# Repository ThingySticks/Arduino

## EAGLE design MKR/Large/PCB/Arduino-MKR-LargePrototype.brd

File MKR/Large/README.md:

Large Prototyping PCB for Arduino MKR Series
============================================

Suitable for:

* Arduino MKR Zero
* Arduino MKR 1000 WiFi
* Arduino MKR FOX 1200
* Arduino MKR WAN 1300
* Arduino MKR GSM 1000

[Available on Tindie](https://www.tindie.com/products/ThingySticks/large-prototype-pcb-for-the-arduino-mkr-series/)

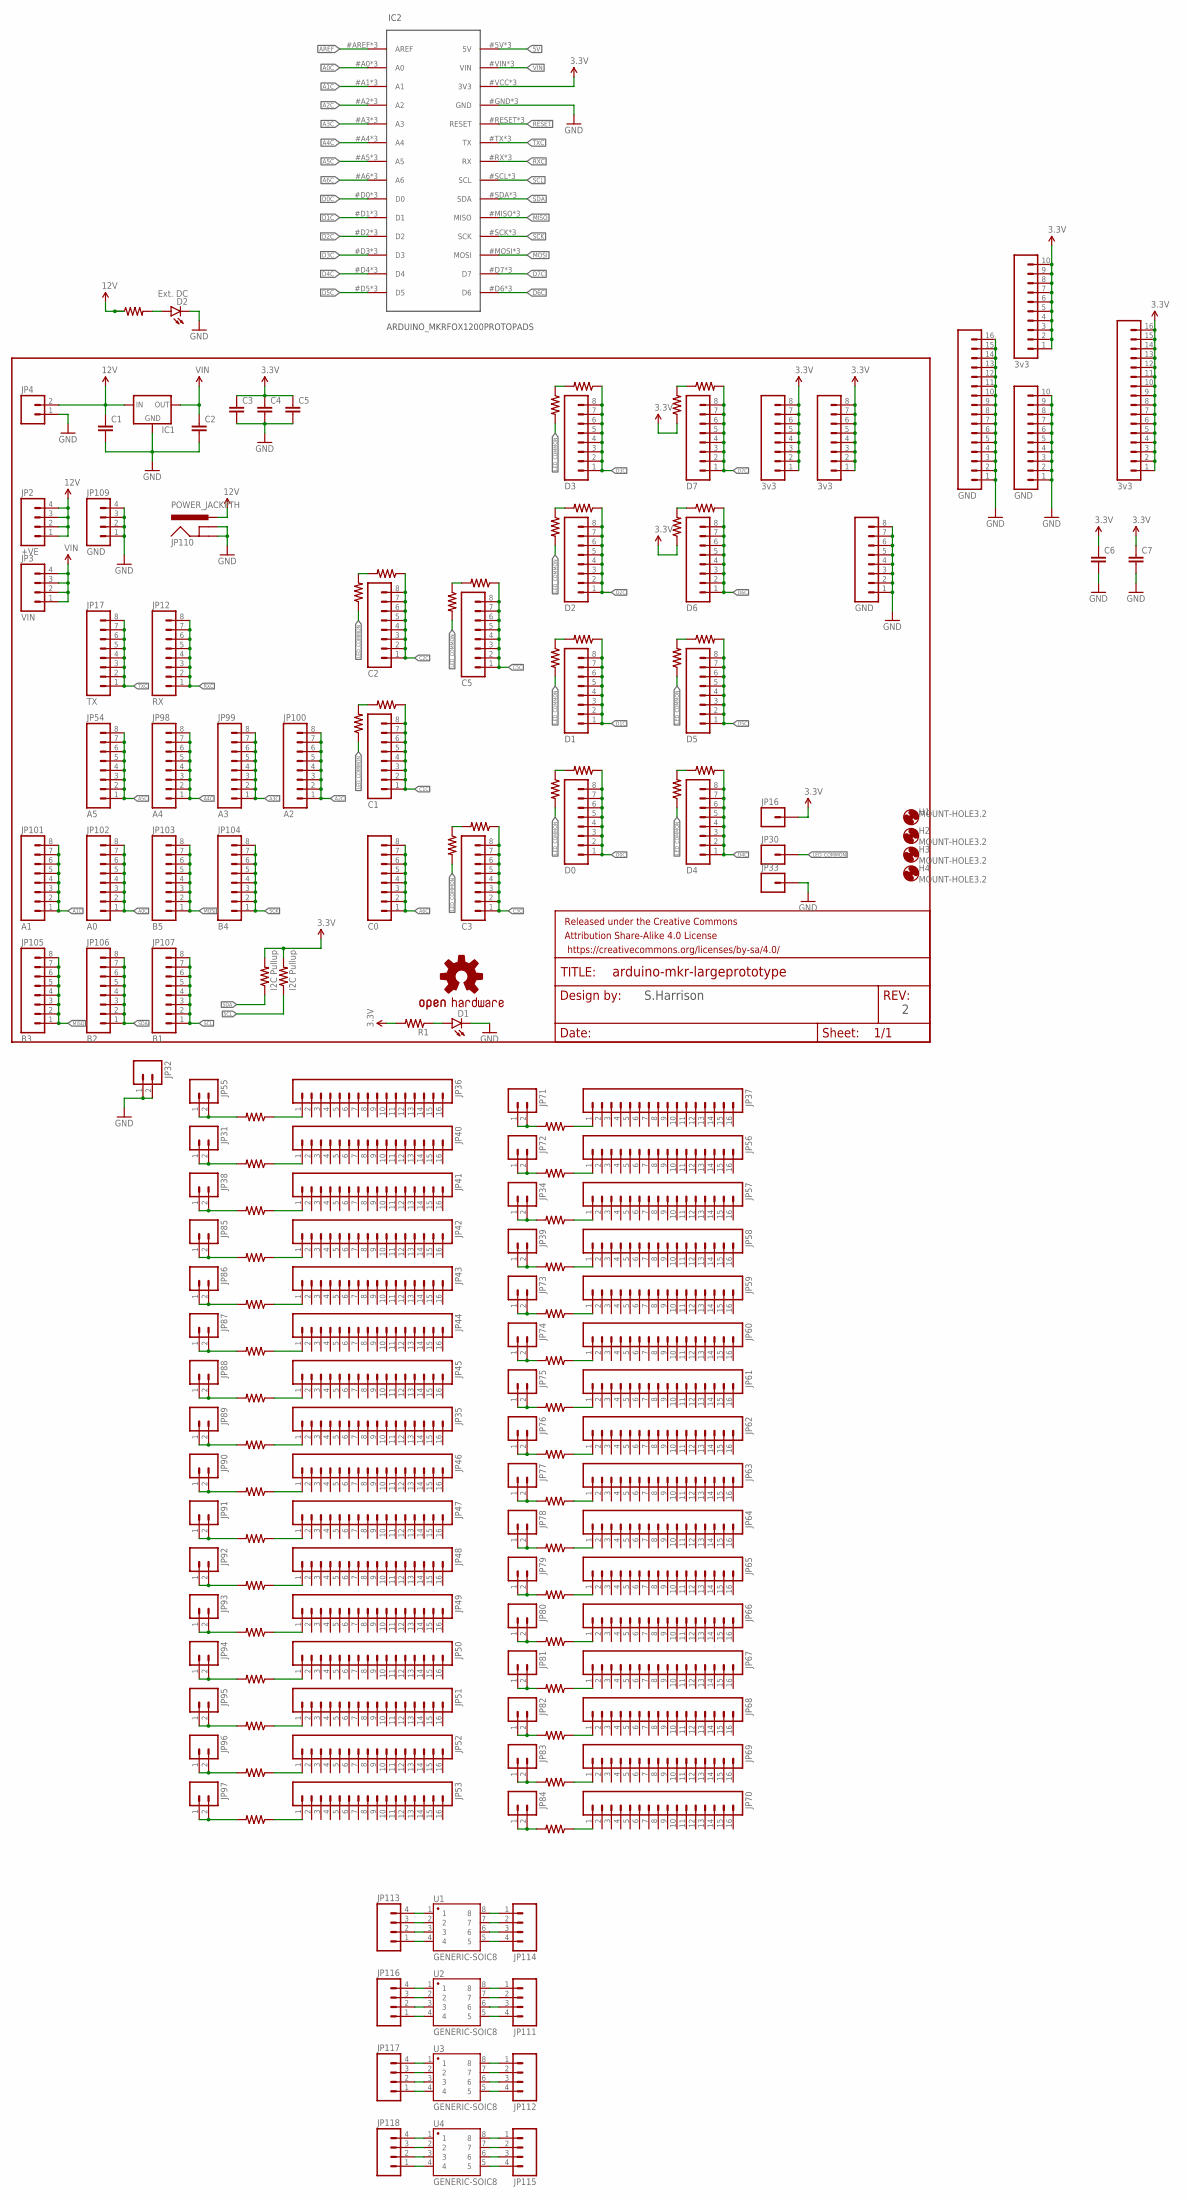
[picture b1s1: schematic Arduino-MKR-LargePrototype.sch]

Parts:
3V1, 3V3: 3v3; 1X08_ROUND
C1, C2, C3, C4, C5, C6, C7: 1UF-25V-10%(0805)"; 0805-CAP
D1: LED1206-BOTTOM; LED-1206-BOTTOM
D2: Ext. DC; LED-1206
FRAME1: FRAME-LETTER; CREATIVE_COMMONS
H1, H2, H3, H4: MOUNT-HOLE3.2; 3,2
IC1: 78XXS
IC2: ARDUINO_MKRFOX1200PROTOPADS; ARDUINO_MKRFOX1200_PROTOPADS
JP1: D7; 1X08_ROUND
JP2: +VE; 1X04
JP3: VIN; 1X04
JP4: M025MM; SCREWTERMINAL-5MM-2
JP5: 3v3; 1X10
JP7: D6; 1X08_ROUND
JP10: D5; 1X08_ROUND
JP11: GND; 1X10
JP12: RX; 1X08_ROUND
JP13: 3v3; 1X16
JP14: GND; 1X16
JP16, JP30, JP33: M01PTH; 1X01
JP17: TX; 1X08_ROUND
JP18: D4; 1X08_ROUND
JP19: D3; 1X08_ROUND
JP20: D2; 1X08_ROUND
JP21: D1; 1X08_ROUND
JP22: D0; 1X08_ROUND
JP23: GND; 1X08_ROUND
JP24: C5; 1X08_ROUND
JP26: C3; 1X08_ROUND
JP27: C2; 1X08_ROUND
JP28: C1; 1X08_ROUND
JP29: C0; 1X08_ROUND
JP31, JP32, JP34, JP38, JP39, JP55, JP71, JP72, JP73, JP74, JP75, JP76, JP77, JP78, JP79, JP80, JP81, JP82, JP83, JP84, JP85, JP86, JP87, JP88, JP89, JP90, JP91, JP92, JP93, JP94, JP95, JP96, JP97: M02PTH; 1X02
JP35, JP36, JP37, JP40, JP41, JP42, JP43, JP44, JP45, JP46, JP47, JP48, JP49, JP50, JP51, JP52, JP53, JP56, JP57, JP58, JP59, JP60, JP61, JP62, JP63, JP64, JP65, JP66, JP67, JP68, JP69, JP70: M161X16_NO_SILK; 1X16_NO_SILK
JP54: A5; 1X08_ROUND
JP98: A4; 1X08_ROUND
JP99: A3; 1X08_ROUND
JP100: A2; 1X08_ROUND
JP101: A1; 1X08_ROUND
JP102: A0; 1X08_ROUND
JP103: B5; 1X08_ROUND
JP104: B4; 1X08_ROUND
JP105: B3; 1X08_ROUND
JP106: B2; 1X08_ROUND
JP107: B1; 1X08_ROUND
JP109: GND; 1X04
JP110: POWER_JACKPTH; POWER_JACK_PTH
JP111, JP112, JP113, JP114, JP115, JP116, JP117, JP118: M04NO_SILK_ALL_ROUND; 1X04_NO_SILK_ALL_ROUND
LOGO3: OSHW-LOGOM; OSHW-LOGO-M
R1, R2, R3, R4, R5, R6, R7, R8, R9, R10, R11, R12, R13, R14, R15, R16, R17, R18, R19, R22, R23, R24, R25, R26, R27, R28, R30, R31, R32, R33, R34, R35, R36, R37, R38, R39, R40, R41, R42, R43, R44, R45, R46, R47, R48, R49, R50, R51, R52, R53, R54, R55, R56, R57, R58, R59, R60, R61: RESISTOR1206; 1206
R64, R65: I2C Pullup; 1206
U1, U2, U3, U4: GENERIC-SOIC8; SO08-UNIVERSAL

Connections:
3.3V: 3V1.1, 3V1.2, 3V1.3, 3V1.4, 3V1.5, 3V1.6, 3V1.7, 3V1.8, 3V3.1, 3V3.2, 3V3.3, 3V3.4, 3V3.5, 3V3.6, 3V3.7, 3V3.8, C3.1, C4.1, C5.1, C6.1, C7.1, IC2.#VCC (3V3), IC2.@VCC (3V3), IC2.VCC (3V3), JP5.1, JP5.2, JP5.3, JP5.4, JP5.5, JP5.6, JP5.7, JP5.8, JP5.9, JP5.10, JP13.1, JP13.2, JP13.3, JP13.4, JP13.5, JP13.6, JP13.7, JP13.8, JP13.9, JP13.10, JP13.11, JP13.12, JP13.13, JP13.14, JP13.15, JP13.16, JP16.1, R1.2, R2.1, R5.1, R64.2, R65.2
5V: IC2.5V, IC2.#5V (5V), IC2.@5V (5V)
12V: C1.1, IC1.IN, JP2.1, JP2.2, JP2.3, JP2.4, JP4.2, JP110.PWR, R28.1
A0C: IC2.#A0 (A0), IC2.@A0 (A0), IC2.A0, JP102.1, JP102.2, JP102.3, JP102.4, JP102.5, JP102.6, JP102.7, JP102.8
A1C: IC2.#A1 (A1), IC2.@A1 (A1), IC2.A1, JP101.1, JP101.2, JP101.3, JP101.4, JP101.5, JP101.6, JP101.7, JP101.8
A2C: IC2.#A2 (A2), IC2.@A2 (A2), IC2.A2, JP100.1, JP100.2, JP100.3, JP100.4, JP100.5, JP100.6, JP100.7, JP100.8
A3C: IC2.#A3 (A3), IC2.@A3 (A3), IC2.A3, JP99.1, JP99.2, JP99.3, JP99.4, JP99.5, JP99.6, JP99.7, JP99.8
A4C: IC2.#A4 (A4), IC2.@A4 (A4), IC2.A4, JP98.1, JP98.2, JP98.3, JP98.4, JP98.5, JP98.6, JP98.7, JP98.8
A5C: IC2.#A5 (A5), IC2.@A5 (A5), IC2.A5, JP54.1, JP54.2, JP54.3, JP54.4, JP54.5, JP54.6, JP54.7, JP54.8
A6C: IC2.#A6 (A6), IC2.@A6 (A6), IC2.A6, JP29.1, JP29.2, JP29.3, JP29.4, JP29.5, JP29.6, JP29.7, JP29.8
AREF: IC2.#AREF (AREF), IC2.@AREF (AREF), IC2.AREF
C1C: JP28.1, JP28.2, JP28.3, JP28.4, JP28.5, JP28.6, JP28.7, JP28.8, R26.1
C2C: JP27.1, JP27.2, JP27.3, JP27.4, JP27.5, JP27.6, JP27.7, JP27.8, R24.1
C3C: JP26.1, JP26.2, JP26.3, JP26.4, JP26.5, JP26.6, JP26.7, JP26.8, R22.1
C5C: JP24.1, JP24.2, JP24.3, JP24.4, JP24.5, JP24.6, JP24.7, JP24.8, R18.1
D0C: IC2.#D0 (D0), IC2.@D0 (D0), IC2.D0, JP22.1, JP22.2, JP22.3, JP22.4, JP22.5, JP22.6, JP22.7, JP22.8, R16.1
D1C: IC2.#D1 (D1), IC2.@D1 (D1), IC2.D1, JP21.1, JP21.2, JP21.3, JP21.4, JP21.5, JP21.6, JP21.7, JP21.8, R14.1
D2C: IC2.#D2 (D2), IC2.@D2 (D2), IC2.D2, JP20.1, JP20.2, JP20.3, JP20.4, JP20.5, JP20.6, JP20.7, JP20.8, R12.1
D3C: IC2.#D3 (D3), IC2.@D3 (D3), IC2.D3, JP19.1, JP19.2, JP19.3, JP19.4, JP19.5, JP19.6, JP19.7, JP19.8, R10.1
D4C: IC2.#D4 (D4), IC2.@D4 (D4), IC2.D4, JP18.1, JP18.2, JP18.3, JP18.4, JP18.5, JP18.6, JP18.7, JP18.8, R8.2
D5C: IC2.#D5 (D5), IC2.@D5 (D5), IC2.D5, JP10.1, JP10.2, JP10.3, JP10.4, JP10.5, JP10.6, JP10.7, JP10.8, R6.2
D6C: IC2.#D6 (D6), IC2.@D6 (D6), IC2.D6, JP7.1, JP7.2, JP7.3, JP7.4, JP7.5, JP7.6, JP7.7, JP7.8, R4.2
D7C: IC2.#D7 (D7), IC2.@D7 (D7), IC2.D7, JP1.1, JP1.2, JP1.3, JP1.4, JP1.5, JP1.6, JP1.7, JP1.8, R3.2
GND: C1.2, C2.2, C3.2, C4.2, C5.2, C6.2, C7.2, D1.C, D2.C, IC1.GND, IC2.#GND (GND), IC2.@GND (GND), IC2.GND, JP4.1, JP11.1, JP11.2, JP11.3, JP11.4, JP11.5, JP11.6, JP11.7, JP11.8, JP11.9, JP11.10, JP14.1, JP14.2, JP14.3, JP14.4, JP14.5, JP14.6, JP14.7, JP14.8, JP14.9, JP14.10, JP14.11, JP14.12, JP14.13, JP14.14, JP14.15, JP14.16, JP23.1, JP23.2, JP23.3, JP23.4, JP23.5, JP23.6, JP23.7, JP23.8, JP32.1, JP32.2, JP33.1, JP109.1, JP109.2, JP109.3, JP109.4, JP110.GND, JP110.GNDBREAK
LED_COMMON: JP30.1, R7.1, R9.1, R11.2, R13.2, R15.2, R17.2, R19.2, R23.2, R25.1, R27.1
MISO: IC2.#MISO (MISO), IC2.@MISO (MISO), IC2.MISO, JP105.1, JP105.2, JP105.3, JP105.4, JP105.5, JP105.6, JP105.7, JP105.8
MOSI: IC2.#MOSI (MOSI), IC2.@MOSI (MOSI), IC2.MOSI, JP103.1, JP103.2, JP103.3, JP103.4, JP103.5, JP103.6, JP103.7, JP103.8
unnamed: D1.A, R1.1
unnamed: JP113.4, U1.1
unnamed: JP113.3, U1.2
unnamed: R4.1, R5.2
unnamed: R2.2, R3.1
unnamed: R10.2, R11.1
unnamed: JP113.2, U1.3
unnamed: JP113.1, U1.4
unnamed: JP114.1, U1.8
unnamed: R8.1, R9.2
unnamed: R6.1, R7.2
unnamed: JP114.2, U1.7
unnamed: R12.2, R13.1
unnamed: R14.2, R15.1
unnamed: R16.2, R17.1
unnamed: JP114.3, U1.6
unnamed: JP114.4, U1.5
unnamed: JP116.4, U2.1
unnamed: R18.2, R19.1
unnamed: JP116.3, U2.2
unnamed: JP116.2, U2.3
unnamed: R22.2, R23.1
unnamed: JP71.1, JP71.2, R46.2
unnamed: JP116.1, U2.4
unnamed: R26.2, R27.2
unnamed: JP117.4, U3.1
unnamed: R24.2, R25.2
unnamed: JP117.3, U3.2
unnamed: JP72.1, JP72.2, R47.2
unnamed: JP34.1, JP34.2, R48.2
unnamed: JP39.1, JP39.2, R49.2
unnamed: JP73.1, JP73.2, R50.2
unnamed: JP74.1, JP74.2, R51.2
unnamed: JP75.1, JP75.2, R52.2
unnamed: JP76.1, JP76.2, R53.2
unnamed: JP77.1, JP77.2, R54.2
unnamed: JP78.1, JP78.2, R55.2
unnamed: JP79.1, JP79.2, R56.2
unnamed: JP80.1, JP80.2, R57.2
unnamed: JP81.1, JP81.2, R58.2
unnamed: JP82.1, JP82.2, R59.2
unnamed: JP83.1, JP83.2, R60.2
unnamed: JP84.1, JP84.2, R61.2
unnamed: JP70.1, R61.1
unnamed: JP69.1, R60.1
unnamed: JP68.1, R59.1
unnamed: JP67.1, R58.1
unnamed: JP66.1, R57.1
unnamed: JP65.1, R56.1
unnamed: JP64.1, R55.1
unnamed: JP63.1, R54.1
unnamed: JP62.1, R53.1
unnamed: JP61.1, R52.1
unnamed: JP60.1, R51.1
unnamed: JP59.1, R50.1
unnamed: JP58.1, R49.1
unnamed: JP57.1, R48.1
unnamed: JP56.1, R47.1
unnamed: JP37.1, R46.1
unnamed: JP97.1, JP97.2, R45.2
unnamed: JP96.1, JP96.2, R44.2
unnamed: JP95.1, JP95.2, R43.2
unnamed: JP94.1, JP94.2, R42.2
unnamed: JP93.1, JP93.2, R41.2
unnamed: JP92.1, JP92.2, R40.2
unnamed: JP91.1, JP91.2, R39.2
unnamed: JP90.1, JP90.2, R38.2
unnamed: JP89.1, JP89.2, R37.2
unnamed: JP88.1, JP88.2, R36.2
unnamed: JP87.1, JP87.2, R35.2
unnamed: JP86.1, JP86.2, R34.2
unnamed: JP85.1, JP85.2, R33.2
unnamed: JP38.1, JP38.2, R32.2
unnamed: JP55.1, JP55.2, R30.2
unnamed: JP36.1, R30.1
unnamed: JP40.1, R31.1
unnamed: JP41.1, R32.1
unnamed: JP42.1, R33.1
unnamed: JP43.1, R34.1
unnamed: JP44.1, R35.1
unnamed: JP45.1, R36.1
unnamed: JP35.1, R37.1
unnamed: JP46.1, R38.1
unnamed: JP47.1, R39.1
unnamed: JP48.1, R40.1
unnamed: JP49.1, R41.1
unnamed: JP50.1, R42.1
unnamed: JP51.1, R43.1
unnamed: JP52.1, R44.1
unnamed: JP53.1, R45.1
unnamed: JP31.1, JP31.2, R31.2
unnamed: D2.A, R28.2
unnamed: JP117.2, U3.3
unnamed: JP117.1, U3.4
unnamed: JP118.4, U4.1
unnamed: JP118.3, U4.2
unnamed: JP118.2, U4.3
unnamed: JP118.1, U4.4
unnamed: JP115.1, U4.8
unnamed: JP115.2, U4.7
unnamed: JP115.3, U4.6
unnamed: JP115.4, U4.5
unnamed: JP112.4, U3.5
unnamed: JP112.3, U3.6
unnamed: JP112.2, U3.7
unnamed: JP112.1, U3.8
unnamed: JP111.4, U2.5
unnamed: JP111.3, U2.6
unnamed: JP111.2, U2.7
unnamed: JP111.1, U2.8
RESET: IC2.#RESET (RESET), IC2.@RESET (RESET), IC2.RESET
RXC: IC2.#RX (RX), IC2.@RX (RX), IC2.RX, JP12.1, JP12.2, JP12.3, JP12.4, JP12.5, JP12.6, JP12.7, JP12.8
SCK: IC2.#SCK (SCK), IC2.@SCK (SCK), IC2.SCK, JP104.1, JP104.2, JP104.3, JP104.4, JP104.5, JP104.6, JP104.7, JP104.8
SCL: IC2.#SCL (SCL), IC2.@SCL (SCL), IC2.SCL, JP107.1, JP107.2, JP107.3, JP107.4, JP107.5, JP107.6, JP107.7, JP107.8, R64.1
SDA: IC2.#SDA (SDA), IC2.@SDA (SDA), IC2.SDA, JP106.1, JP106.2, JP106.3, JP106.4, JP106.5, JP106.6, JP106.7, JP106.8, R65.1
TXC: IC2.#TX (TX), IC2.@TX (TX), IC2.TX, JP17.1, JP17.2, JP17.3, JP17.4, JP17.5, JP17.6, JP17.7, JP17.8
VIN: C2.1, IC1.OUT, IC2.#VIN (VIN), IC2.@VIN (VIN), IC2.VIN, JP3.1, JP3.2, JP3.3, JP3.4

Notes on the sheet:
S.Harrison

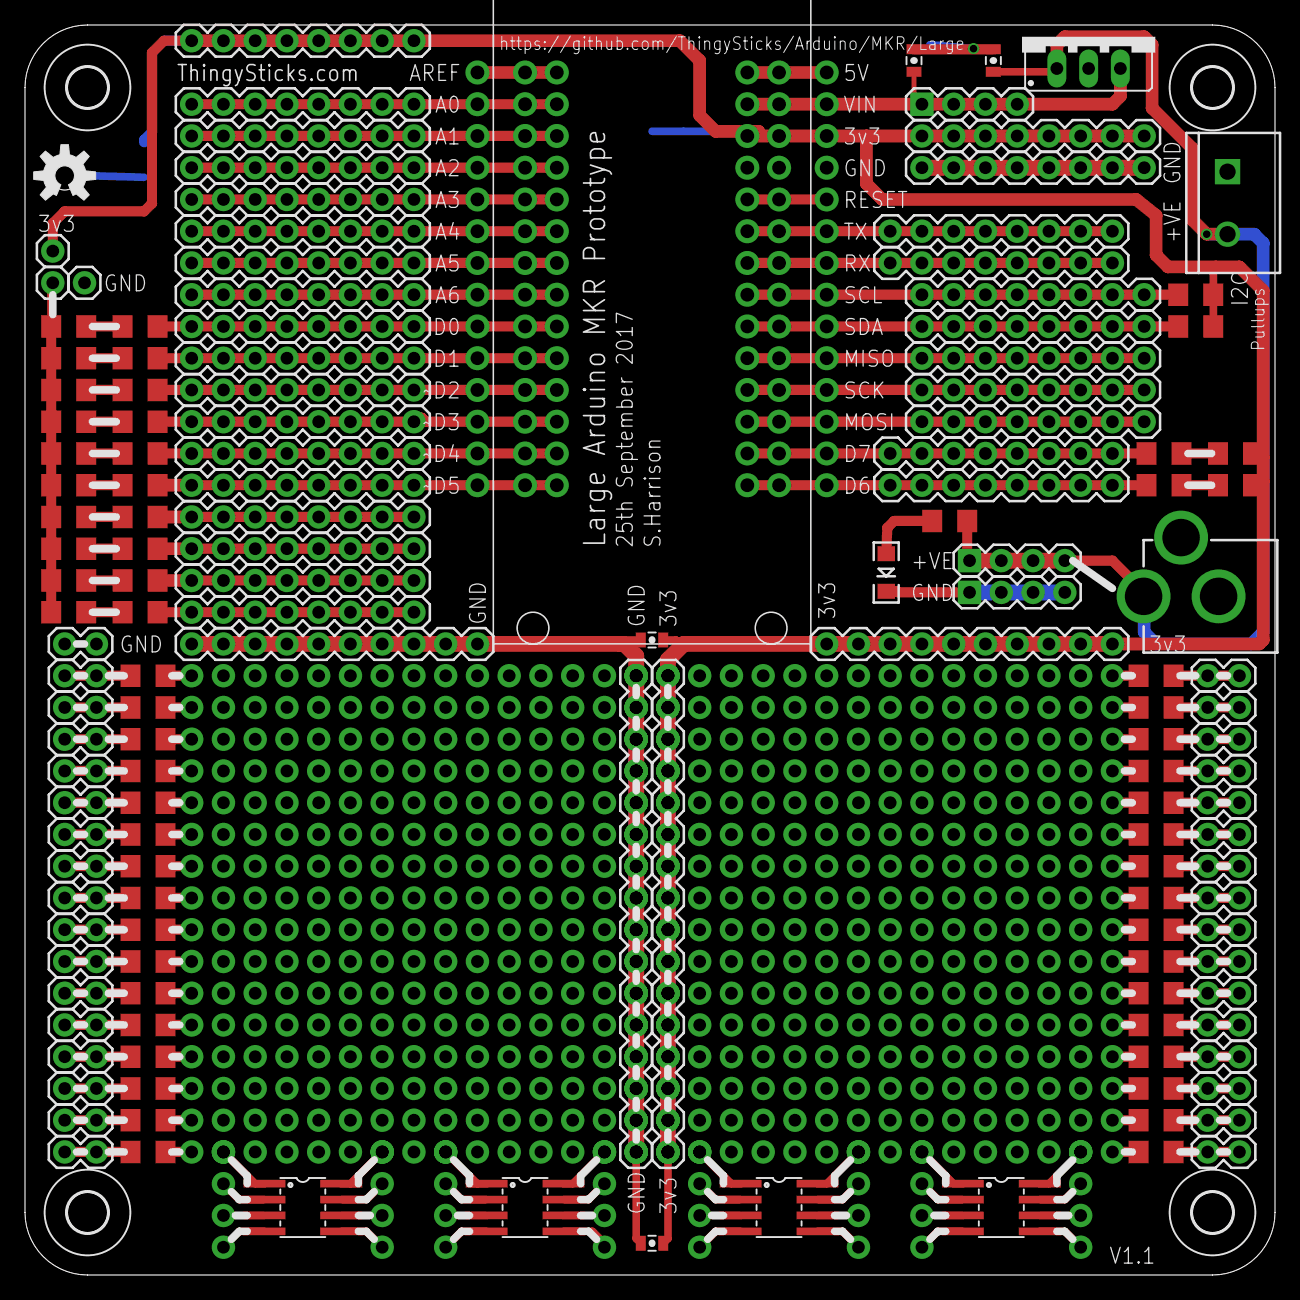
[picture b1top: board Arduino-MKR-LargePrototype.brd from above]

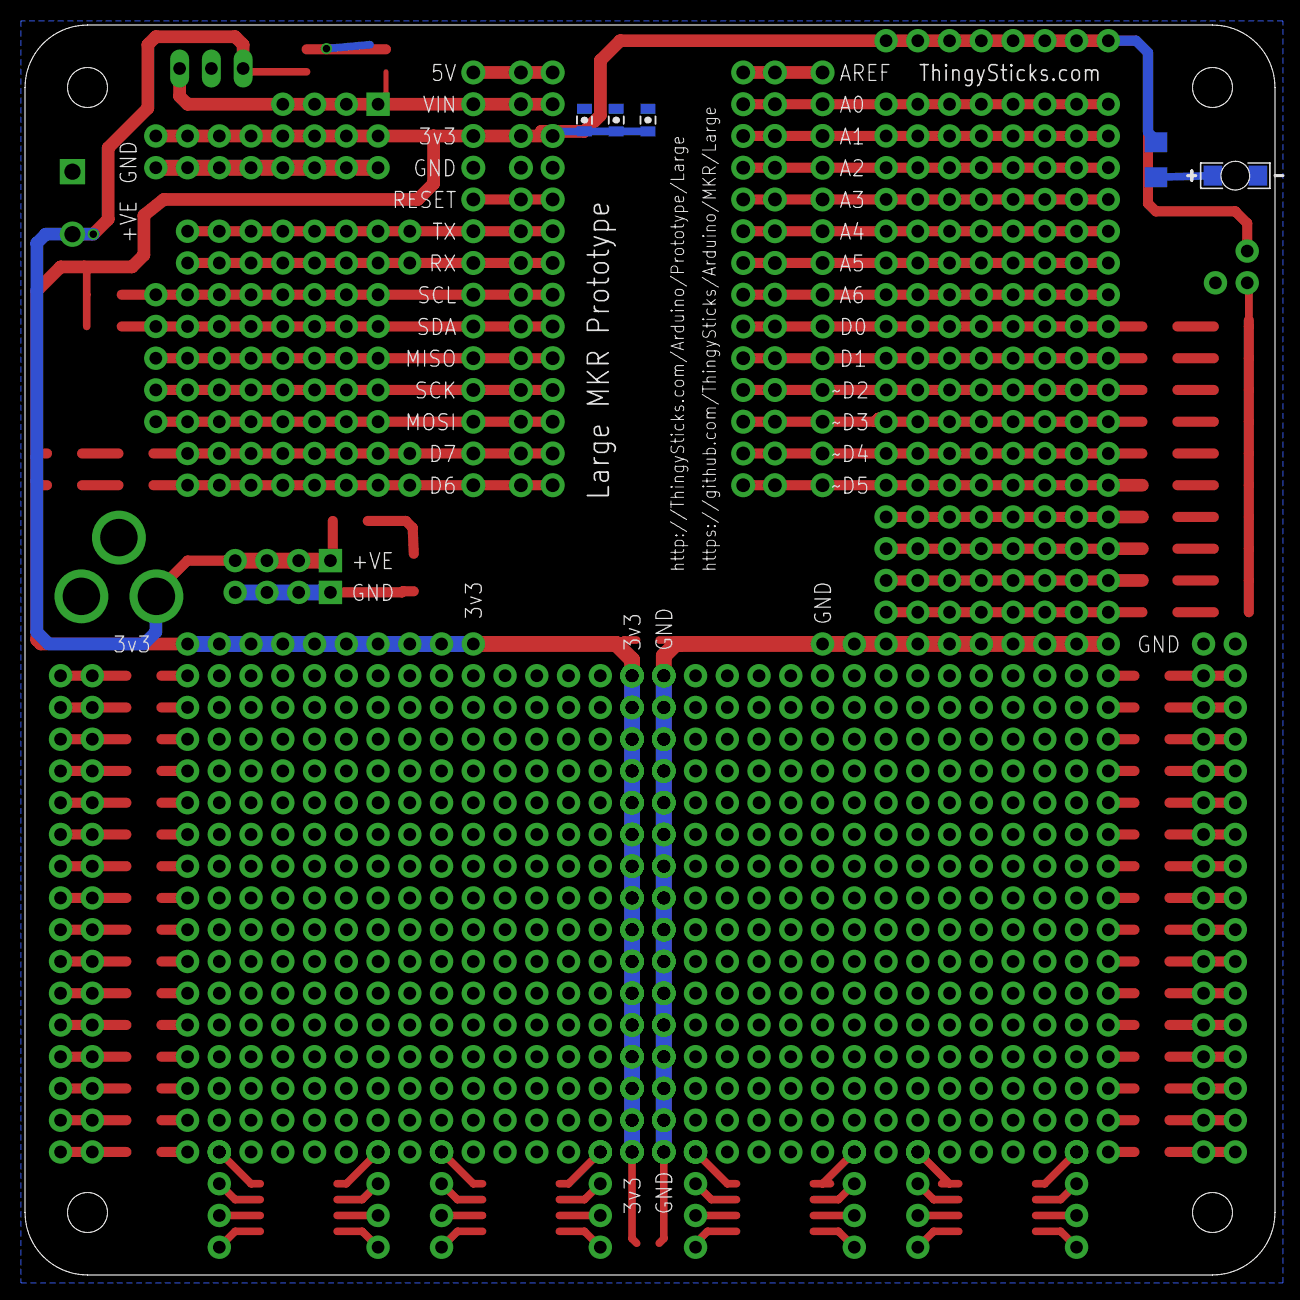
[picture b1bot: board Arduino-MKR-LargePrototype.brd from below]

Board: 2 copper layers, 100.0 x 100.0 mm, 195 parts (5 on the bottom side), 144 nets.

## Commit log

2017-08-13 Initial version of the large (10x10) prototype PCB
2017-09-25 Updated links and name to make it not MKRFox1200 specific as the pinout is the same for WiFi
2017-09-25 Fixed up filenames and paths and all that.
2017-09-25 Added PCB images from DirtyPCBs.
2017-09-25 Added 3D Printable base
2017-09-25 Added gitignore
2017-11-23 Added PCB layout images.
2017-11-27 Added readme for large MKR series prototype

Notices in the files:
parts and their libraries:
SparkFun-Capacitors: Licensing: Creative Commons ShareAlike 4.0 International - https://creativecommons.org/licenses/by-sa/4.0
SparkFun-Aesthetics: Released under the Creative Commons Attribution Share-Alike 4.0 License
SparkFun-Aesthetics: https://creativecommons.org/licenses/by-sa/4.0
